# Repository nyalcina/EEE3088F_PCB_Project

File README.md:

# EEE3088F_PCB_Project_PTXNYA001_MNGAMO004
This repository details the progress of a Micromouse Power Board which was assigned by the EEE3088F teaching staff of the University of Cape Town. This project was completed in collaboration between Nyakallo Peete and Amos Manganye.
# Micro-Mouse Power Subsystem

---

## Overview

This repository contains the design files, schematics, and documentation for the **Power Subsystem** of the 2025 Micro-Mouse Project, developed as part of the EEE3088F course.

The Power Subsystem is responsible for:
- Accepting 9V input from a USB-C Power Delivery (PD) source.
- Charging a 3.7V 800mAh LiPo battery with selectable charging modes.
- Supplying regulated 3.3V and 5V outputs to system modules and motors.
- Controlling system power states through a low-leakage ON/OFF switch.
- Monitoring battery voltage and current via an I²C bus.
- Driving four motors (primary and auxiliary) for micro-mouse navigation.

---

## Features

- Provides regulated 5V and 3.3V outputs to supply all system modules, including processors, sensors, and external loads.
- Powers four motors (bidirectionally) via integrated motor driver outputs for primary and auxiliary drive control.
- Supports charging of a 3.7V 800mAh LiPo battery from a 9V USB-C input.
- Offers two selectable battery charging modes: low current mode (for extended battery life) and high current mode (for faster charging).
- Includes an ON/OFF control system that completely disables power rails when not in use, reducing standby current to less than 30μA.
- Enables real-time battery voltage and current monitoring through an I²C interface for improved system diagnostics and safety.
- Provides jumper-based power isolation and multiple test points throughout the system to simplify testing, debugging, and future upgrades.
- Designed for compact size, robustness, low cost, and manufacturability using JLCPCB basic part components.

---

## Tools Used

- KiCad 9.0 for schematic and PCB layout
- EasyEDA for footprints
- GitHub for version control and project documentation
- JLCBPB for manufacturing

---

## Authors

- **Amos Manganye**
- **Nyakallo Peete**

---

## Acknowledgements

- University of Cape Town (UCT) — Department of Electrical Engineering
- EEE3088F Teaching Staff

---

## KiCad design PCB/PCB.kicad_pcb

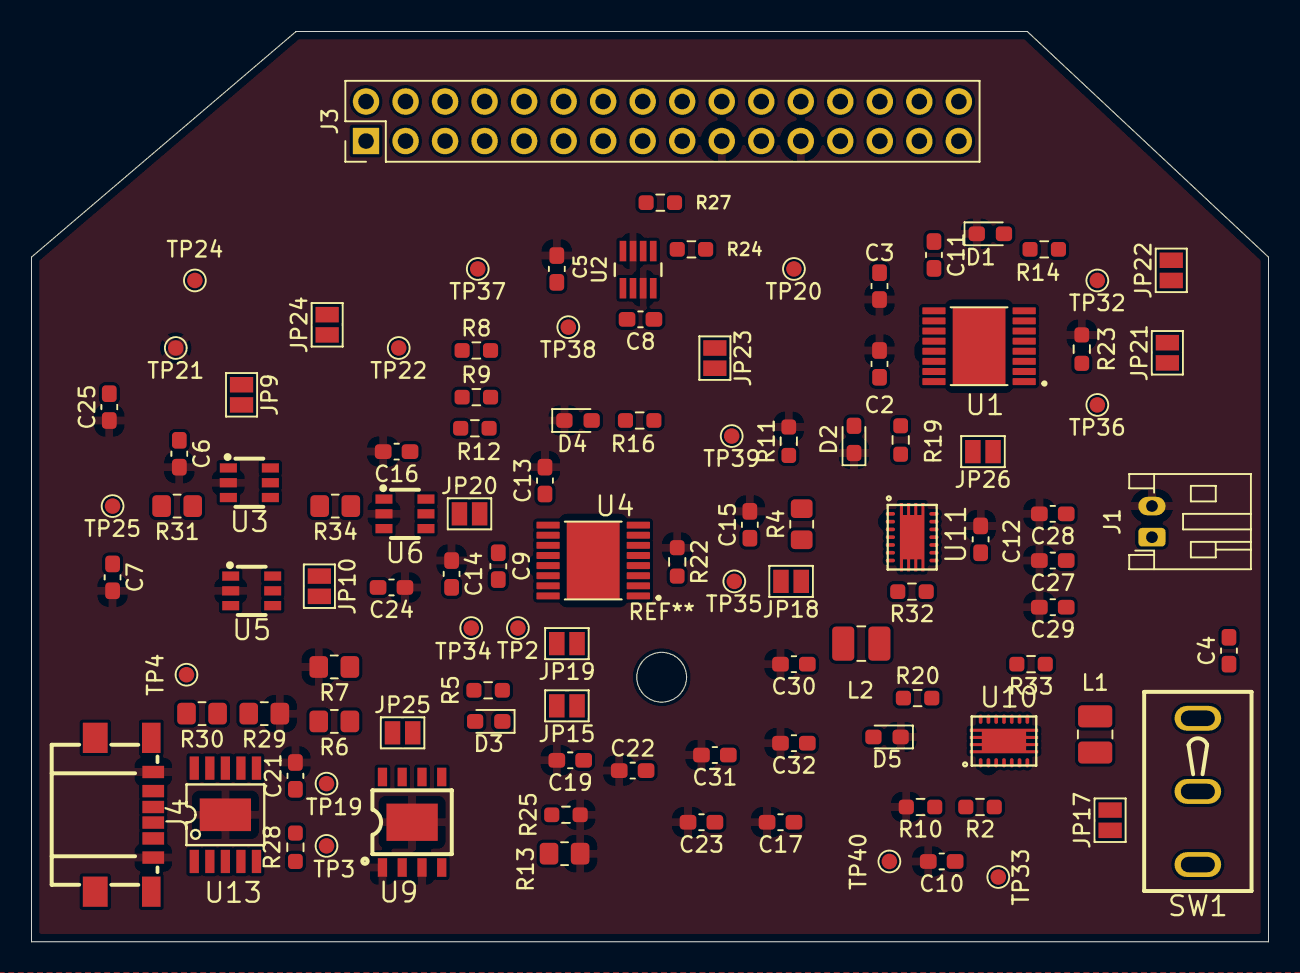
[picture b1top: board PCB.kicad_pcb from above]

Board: 2 copper layers, 79.5 x 58.5 mm, 107 parts (0 on the bottom side), 78 nets, no tracks yet.

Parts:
C2, C14: 2.2u; C_0603_1608Metric_Pad1.08x0.95mm_HandSolder
C3, C6, C7, C12, C13, C16, C17, C19, C22, C23, C24, C25: 10u; C_0603_1608Metric_Pad1.08x0.95mm_HandSolder
C4, C21: 1u; C_0603_1608Metric_Pad1.08x0.95mm_HandSolder
C5, C8, C9, C10, C11, C15: 100n; C_0603_1608Metric_Pad1.08x0.95mm_HandSolder
C27, C28, C29, C30, C31, C32: 22u; C_0603_1608Metric_Pad1.08x0.95mm_HandSolder
D1, D2, D4, D5: LED; LED_0603_1608Metric_Pad1.05x0.95mm_HandSolder
D3: Red; LED_0603_1608Metric_Pad1.05x0.95mm_HandSolder
J1: Conn_01x02_Pin; JST_PH_S2B-PH-K_1x02_P2.00mm_Horizontal
J3: Conn_02x16_Odd_Even; PinHeader_2x16_P2.54mm_Vertical
J4: USB_C_Receptacle_PowerOnly_6P; USB-C-SMD_TYPE-602-T3
JP9, JP10, JP15, JP17, JP18, JP19, JP20, JP21, JP22, JP23, JP24, JP25, JP26: Jumper_2_Small_Open; SolderJumper-2_P1.3mm_Open_Pad1.0x1.5mm
L1, L2: 2.2u; L_1008_2520Metric_Pad1.43x2.20mm_HandSolder
R2, R32, R33: 510k; R_0603_1608Metric_Pad0.98x0.95mm_HandSolder
R4: 470k; R_0805_2012Metric_Pad1.20x1.40mm_HandSolder
R5, R14, R16, R19, R20, R28: 1k; R_0603_1608Metric_Pad0.98x0.95mm_HandSolder
R6, R30, R31, R34: 10k; R_0805_2012Metric_Pad1.20x1.40mm_HandSolder
R7: 8.2k; R_0805_2012Metric_Pad1.20x1.40mm_HandSolder
R8, R9, R12, R22, R23: 0.22; R_0603_1608Metric_Pad0.98x0.95mm_HandSolder
R10: 56k; R_0603_1608Metric_Pad0.98x0.95mm_HandSolder
R11: 82k; R_0603_1608Metric_Pad0.98x0.95mm_HandSolder
R13: 5k6; R_0805_2012Metric_Pad1.20x1.40mm_HandSolder
R24, R27: 4.7k; R_0603_1608Metric_Pad0.98x0.95mm_HandSolder
R25: 1k8; R_0603_1608Metric_Pad0.98x0.95mm_HandSolder
R29: 6k8; R_0805_2012Metric_Pad1.20x1.40mm_HandSolder
SW1: SW_Nidec_CAS-120A1; SW-TH_1MS1T1B1M1QES-5
TP2, TP3, TP4, TP19, TP20, TP21, TP22, TP24, TP25, TP32, TP33, TP34, TP35, TP36, TP37, TP38, TP39, TP40: TestPoint; TestPoint_Pad_D1.0mm
U1: DRV8833PWPR; IC_DRV8833PWPR
U2: INA219AxDCN; INA219AIDCNR
U3, U5: TPS22917DBV; SOT-23-6_L2.9-W1.6-P0.95-LS2.8-BR
U4: DRV8833PWP; IC_DRV8833PWPR
U6: TS5A3159ADBVR; SOT-23-6_L2.9-W1.6-P0.95-LS2.8-BR
U9: TP4056-42-ESOP8; ESOP-8_L4.9-W3.9-P1.27-LS6.0-BL-EP
U10, U11: TPS63020; TPS63020DSJR
U13: CH224K; ESSOP-10_L4.9-W3.9-P1.0-LS6.0-TL-EP

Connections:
3V3 Out: J3.18, JP20.1 (A), JP26.1 (A), R4.1
5V Out: C3.1, C6.1, C7.1, C9.1, C11.1, C13.1, J3.20, JP17.1 (A), R2.1, U1.12 (VM), U3.1 (VIN), U3.4 (CT), U4.12 (VM), U5.1 (VIN), U5.4 (CT)
/3V3_Out: JP18.2 (B), JP25.2 (B), TP19.1
/CC1: J4.A5 (CC1), U13.7 (CC1)
/CC2: J4.B5 (CC2), U13.6 (CC2)
/M1AO2: JP21.1 (A), U1.4 (AOUT2)
/M2BO2: JP22.1 (A), U1.5 (BOUT2)
/M3AO2: JP23.1 (A), U4.4 (AOUT2)
/M4BO2: JP24.1 (A), U4.5 (BOUT2)
/SEN1: R23.2, U1.3 (AISEN), U1.6 (BISEN)
/SEN2: R22.2, U4.3 (AISEN), U4.6 (BISEN)
Battery: C4.1, C5.1, C8.1, J3.14, R8.1, R9.1, R12.1, R24.1, R27.1, SW1.1 (C), TP37.1, U1.1 (~SLEEP), U2.1 (IN+), U2.4 (VS), U2.8 (A1), U4.1 (~SLEEP)
CTRL_EXT_LOAD1: J3.25, U3.3 (ON)
CTRL_EXT_LOAD2: J3.7, U5.3 (ON)
Charger: JP19.1 (A), SW1.3 (A)
EXT_LOAD1_OUT: C25.2, J3.21, JP9.2 (B)
EXT_LOAD2_OUT: C24.2, J3.11, JP10.2 (B)
FAST_CHARGE_CTRL: J3.13, U6.6 (IN)
GND: C2.1, C3.2, C5.2, C6.2, C7.2, C10.2, C12.2, C13.2, C14.1, C15.2, C16.2, C17.2, C19.2, C21.2, C22.1, C23.2, C24.1, C25.1, C27.2, C28.2, C29.2, C30.2, C31.2, C32.2, D1.1 (K), D2.1 (K), D4.1 (K), D5.1 (K), J1.2, J3.19, J3.23, J4.A12 (GND), J4.B12 (GND), R7.2, R10.2, R11.2, R13.1, R22.1, R23.1, R25.1, R29.1, TP21.1, U1.13 (GND), U1.17 (GND), U2.3 (GND), U2.7 (A0), U3.2 (GND), U4.13 (GND), U4.17 (GND), U5.2 (GND), U6.2 (GND), U9.1 (TEMP), U9.3 (GND), U9.9 (EPAD), U10.2 (GND), U11.2 (GND), U13.11 (GND)
High_Voltage_(9V): J3.22, J4.A9 (VBUS), J4.B9 (VBUS), R6.1, R28.1, R30.2, TP3.1, TP4.1
I2C1_SCL: J3.16, R24.2, U2.5 (SCL)
I2C1_SDA: J3.17, R27.2, U2.6 (SDA)
Load_Supply: C4.2, C8.2, C12.1, C16.1, C17.1, C23.1, R8.2, R9.2, R12.2, TP38.1, U2.2 (IN-), U10.10 (VIN2), U10.11 (VIN1), U11.10 (VIN2), U11.11 (VIN1)
MOTOR1_A_OUT: J3.32, TP36.1, U1.2 (AOUT1)
MOTOR1_B_OUT: J3.31, JP21.2 (B)
MOTOR1_CTRL1: J3.28, U1.16 (AIN1)
MOTOR1_CTRL2: J3.30, U1.15 (AIN2)
MOTOR2_A_OUT: J3.2, TP32.1, U1.7 (BOUT1)
MOTOR2_B_OUT: J3.1, JP22.2 (B)
MOTOR2_CTRL1: J3.4, U1.9 (BIN1)
MOTOR2_CTRL2: J3.6, U1.10 (BIN2)
MOTOR3_A_OUT: J3.27, TP20.1, U4.2 (AOUT1)
MOTOR3_B_OUT: J3.29, JP23.2 (B)
MOTOR3_CTRL1: J3.24, U4.16 (AIN1)
MOTOR3_CTRL2: J3.26, U4.15 (AIN2)
MOTOR4_A_OUT: J3.3, TP22.1, U4.7 (BOUT1)
MOTOR4_B_OUT: J3.5, JP24.2 (B)
MOTOR4_CTRL1: J3.8, U4.9 (BIN1)
MOTOR4_CTRL2: J3.10, U4.10 (BIN2)
unnamed: D1.2 (A), R14.1
unnamed: D2.2 (A), R19.1
unnamed: D3.2 (A), R5.2
unnamed: D3.1 (K), U9.7 (~CHRG)
unnamed: D4.2 (A), R16.1
unnamed: D5.2 (A), R20.1
unnamed: J1.1, SW1.2 (B)
unnamed: JP9.1 (A), R34.2, TP24.1, U3.6 (VOUT)
unnamed: JP10.1 (A), R31.2, TP25.1, U5.6 (VOUT)
unnamed: C19.1, JP15.1 (A), R5.1, U9.4 (V_{CC}), U9.8 (CE)
unnamed: JP15.2 (B), R6.2, R7.1, TP34.1
unnamed: C30.1, C31.1, C32.1, JP17.2 (B), R33.2, TP33.1, U10.4 (VOUT1), U10.5 (VOUT2)
unnamed: C22.2, JP19.2 (B), TP2.1, U9.5 (BAT)
unnamed: JP20.2 (B), U6.5 (V+)
unnamed: C21.1, JP25.1 (A), R28.2, U13.1 (VDD)
unnamed: C27.1, C28.1, C29.1, JP26.2 (B), R32.2, TP35.1, U11.4 (VOUT1), U11.5 (VOUT2)
unnamed: L1.1, U10.6 (L2), U10.7 (L2)
unnamed: L1.2, U10.8 (L1), U10.9 (L1)
unnamed: L2.1, U11.6 (L2), U11.7 (L2)
unnamed: L2.2, U11.8 (L1), U11.9 (L1)
unnamed: C11.2, U1.11 (VCP)
unnamed: C2.2, U1.14 (VINT)
unnamed: R14.2, U1.8 (~FAULT)
unnamed: R34.1, U3.5 (QOD)
unnamed: C9.2, U4.11 (VCP)
unnamed: C14.2, U4.14 (VINT)
unnamed: R16.2, U4.8 (~FAULT)
unnamed: R31.1, U5.5 (QOD)
unnamed: U6.4 (COM), U9.2 (PROG)
unnamed: R13.2, U6.3 (NC)
unnamed: R25.2, U6.1 (NO)
unnamed: C10.1, U10.1 (VINA), U10.12 (EN), U10.13 (PS/SYNC)
unnamed: R2.2, R10.1, TP40.1, U10.3 (FB)
unnamed: R20.2, R33.1, U10.14 (PG)
unnamed: C15.1, U11.1 (VINA), U11.12 (EN), U11.13 (PS/SYNC)
unnamed: R4.2, R11.1, TP39.1, U11.3 (FB)
unnamed: R19.2, R32.1, U11.14 (PG)
unnamed: R29.2, U13.9 (CFG1)
unnamed: R30.1, U13.8 (VBUS)

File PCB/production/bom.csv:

Designator,Footprint,Quantity,Value,LCSC Part #
"C10, C15",0603,2,100n,C14663
"C11, C12, C14, C19, C22, C3",0603,6,10u,C19702
"C13, C16, C17",0603,3,2.2u,C23630
C2,0603,1,2.2u, C23630
"C21, C4",0603,2,1u,C5673
C5,0603,1,0.1u, C14663
"C6, C7",0603,2,10u,  C19702
"C8, C9",0805,2,47u,C16780
"D1, D2, D4, D5",0603,4,LED,C2286
D3,0603,1,Red,C2286
J1,JST_JWPF_B02B-JWPF-SK-R_1x02_P2.00mm_Vertical,1,Conn_01x02_Pin,
J3,PinHeader_2x16_P2.54mm_Vertical,1,Conn_02x16_Odd_Even,
J4,USB-C-SMD_TYPE-602-T3,1,USB_C_Receptacle_PowerOnly_6P,C2927028
"JP10, JP11, JP12, JP14, JP15, JP16, JP17, JP18, JP19, JP20, JP21, JP22, JP23, JP24, JP25, JP26, JP27, JP28, JP29, JP9",SolderJumper-2_P1.3mm_Open_Pad1.0x1.5mm,20,Jumper_2_Small_Open,
"L1, L2",1008,2,2.2u, C5832372
R10,0805,1,200,C2933534
R11,0603,1,100,C22775
R13,0805,1,5k6,C4382
"R14, R16, R19, R20, R28, R5",0603,6,1k,C21190
"R18, R8, R9",0603,3,0.22, C2960770
R2,0603,1,1.8k, C4177
"R21, R22, R23",0603,3,0.22,C3013347
"R24, R27",0603,2,4.7k,C23162
R25,0603,1,1k8,C4177
R29,0805,1,6k8,C17772
"R30, R31, R32, R6",0805,4,10k,C17414
R4,0603,1,560,C23204
R7,0805,1,8.2k,C17828
SW1,SW-TH_1MS1T1B1M1QES-5,1,SW_Nidec_CAS-120A1,C496154
"TP10, TP11, TP12, TP13, TP14, TP19, TP2, TP20, TP21, TP22, TP23, TP24, TP25, TP26, TP27, TP3, TP30, TP32, TP33, TP34, TP35, TP36, TP37, TP38, TP39, TP4, TP40, TP6, TP7, TP8, TP9",TestPoint_Pad_D1.0mm,31,TestPoint,
U1,IC_DRV8833PWPR,1,DRV8833PWPR,C50506
"U10, U11",TPS63020DSJR,2,TPS63020,C15483
U12,SOT-23-6_L2.9-W1.6-P0.95-LS2.8-BR,1,TS5A3159ADBVR,C128405
U13,ESSOP-10_L4.9-W3.9-P1.0-LS6.0-TL-EP,1,CH224K,C970725
U2,INA219AIDCNR,1,INA219AxDCN,C87469
"U3, U5",SOT-23-6_L2.9-W1.6-P0.95-LS2.8-BR,2,TPS22917DBV, C2681320
U4,IC_DRV8833PWPR,1,DRV8833PWP,C50506
U9,ESOP-8_L4.9-W3.9-P1.27-LS6.0-BL-EP,1,TP4056-42-ESOP8,C16581

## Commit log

2025-03-12 Add kicad files
2025-03-12 Add Project Documentation
2025-03-24 Add ICs without configuration
2025-03-24 Pin Headers added with global labels
2025-03-24 Fix header labels and Add Charger IC
2025-03-24 Semi configured schematic
2025-03-25 Changes to Layout
    - An additional sheet was added
    - ptxnya001's modules were placed into demarcated areas on her sheet
    - ptxnya001's modules were given brief descriptions
2025-03-25 Updated Voltage regulator circuit
2025-03-25 IC footprints and H-bridge test points
2025-03-26 Add Chrarging circuit, USB integration, and pin headers
2025-03-26 Dummy commit
2025-03-26 Hopeful
2025-03-26 Taken back
    This commit is to allow my partner to add his schematic to my previous version.
2025-03-26 Add Charging circuit and USB integration
2025-03-26 Add 2x16 connectors
2025-03-26 Add digital switch for fast charging
2025-03-26 Fix negotiator configuration
2025-03-27 Add H-Bridge footprints
2025-03-27 Add footprint for charging circuit and usb integration
2025-03-27 Fix electrical faults
2025-03-27 Work before Amos's footprint additions
2025-03-27 Fix passive components footprints
2025-03-27 Error Resolutions
2025-03-28 Confirm LCSC numbers
2025-03-28 Double Checking footprints and LCSC numbers
2025-03-28 Before PCB layout
2025-03-28 Begining of PCB Layout
2025-04-04 Fix PCB layout
2025-04-07 Final updates to the INA219, Motor controllers, Voltage regulators and External load switching circuit
2025-04-07 Addition of the RQOD resistor
    The resistor between the QOD and VOUT pins was mistakenly omitted.
2025-04-08 Final Component checks before routing
2025-04-09 Placing All components onto the silkscreen
2025-04-09 Routing
2025-04-09 Done
2025-04-25 Final Schematic edits
2025-04-25 Organised Git Files

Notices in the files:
README.md:
License: MIT
